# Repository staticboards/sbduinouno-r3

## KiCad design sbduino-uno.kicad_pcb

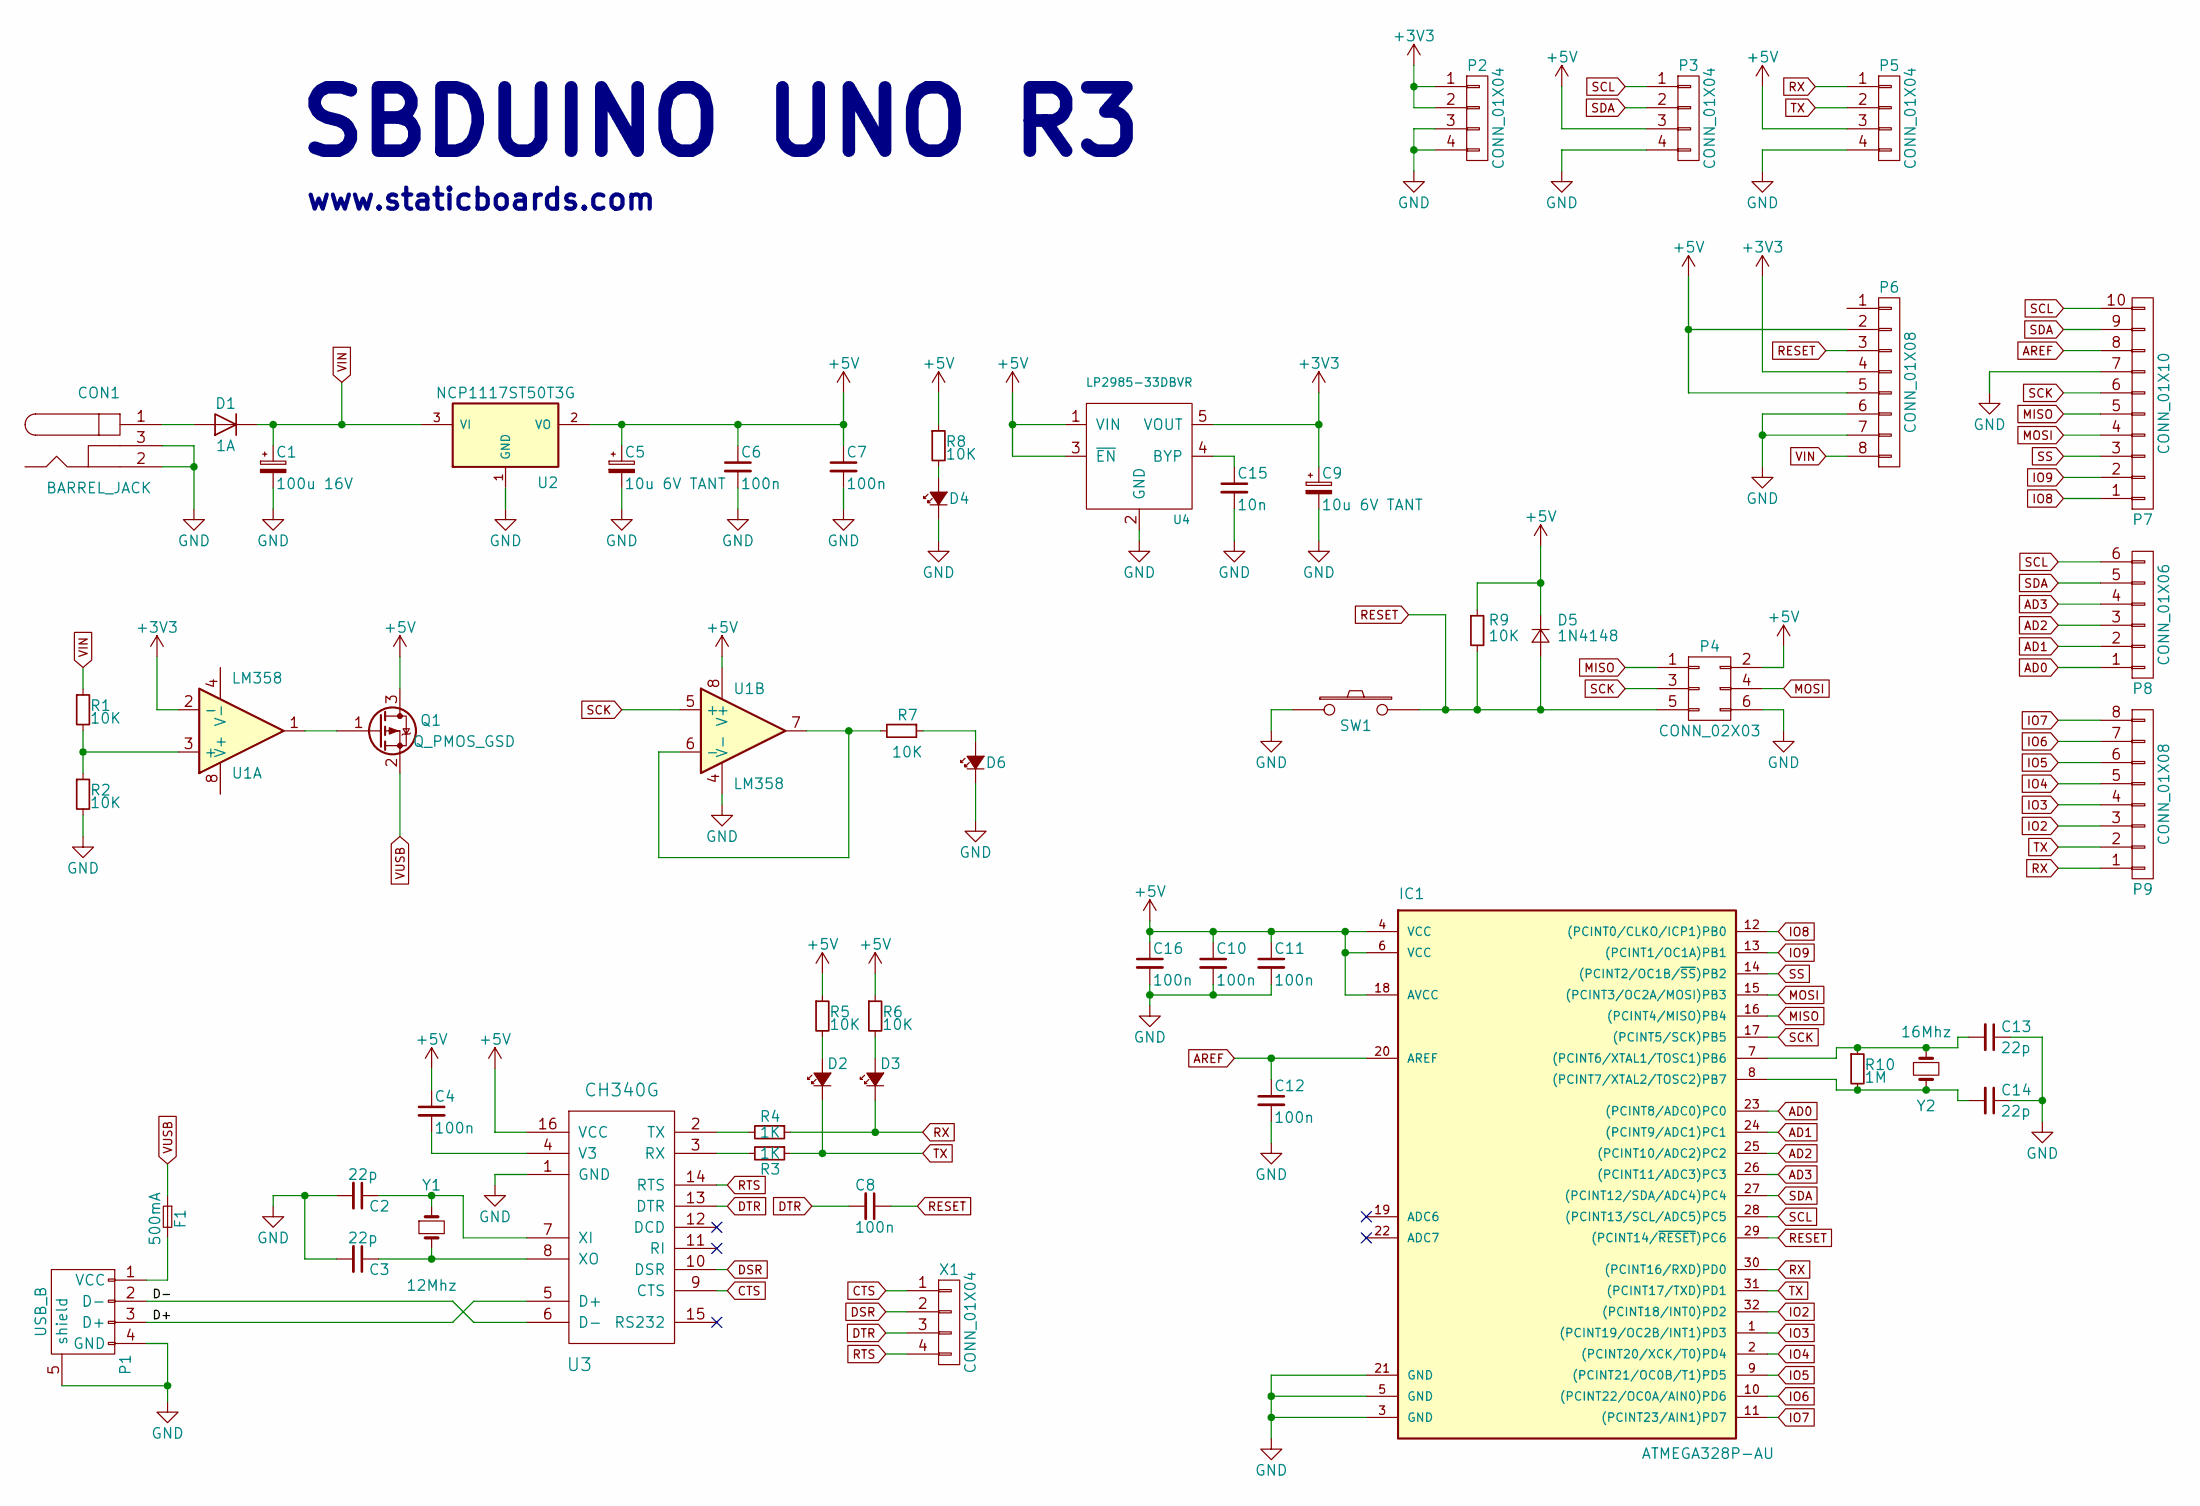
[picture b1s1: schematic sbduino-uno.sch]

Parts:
C1: 100u 16V; CP_Elec_6.3x7.7; Mouser 598-AVE107M25X16T-F
C2, C3, C14: 22p; C_0805
C4, C6, C7, C8, C10, C11, C12, C16: 100n; C_0805
C5, C9: 10u 6V TANT; TantalC_SizeA_EIA-3216_Reflow; Mouser 74-TP3A106K016C1700A
C13: 22p; C_0805; Mouser 81-GRM21A5C2D220JW1D
C15: 10n; C_0805; Mouser 603-CC805MRY5V9BB103
CON1: BARREL_JACK; Mouser 490-PJ-202A
D1: 1A; SMA_Standard; Mouser 625-RS1A-E3
D2, D3, D4: Led_Small; LED_0805
D5: 1N4148; SOD-323; Mouser 621-1N4448WSF-7
D6: Led_Small; LED_0805; Mouser 621-1N4448WSF-7
F1: 500mA; Fuse_SMD1206_Reflow; Mouser 576-1206L050YR
IC1: ATMEGA328P-AU; TQFP-32_7x7mm_Pitch0.8mm
P1: USB_B
P2, P3, P5: CONN_01X04; Pin_Header_Straight_1x04
P4: CONN_02X03; Pin_Header_Straight_2x03
P6, P9: CONN_01X08; Pin_Header_Straight_1x08
P7: CONN_01X10; Pin_Header_Straight_1x10
P8: CONN_01X06; Pin_Header_Straight_1x06
Q1: Q_PMOS_GSD; SOT-23; Mouser 781-SI2301BDS-E3
R1, R2, R5, R6, R7, R8, R9: 10K; R_0805
R3, R4: 1K; R_0805
R10: 1M; R_0805; Mouser 660-RK73H2ATTD1004F
SW1: SW_PUSH; SW_SPST_EVPBF; Mouser 611-PTS645SM43SMTR92
U1: LM358; MSOP-8_3x3mm_Pitch0.65mm; Mouser 595-LMV358IDGKR
U2: NCP1117ST50T3G; SOT-223; Mouser 863-NCP1117ST50T3G
U3: CH340G; SO-16-N
U4: LP2985-33DBVR; SOT-23-5; Mouser 595-LP2985-33DBVR
X1: CONN_01X04; Pin_Header_Straight_1x04
Y1: 12Mhz; Crystal_HC49-SD_SMD; Mouser 815-ABLS-12.0M-T
Y2: 16Mhz; CRYSTAL-SMD-3.2x2.5; Mouser 815-ABM8-16-B2-T

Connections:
+3V3: C9.1, P2.1, P2.2, P6.4, U1.2 (-), U4.5 (VOUT); also elsewhere on the board
+5V: C4.1, C5.1, C6.1, C7.1, C10.1, C11.1, C16.1, D5.1 (K), IC1.4 (VCC), IC1.6 (VCC), IC1.18 (AVCC), P3.3, P4.2, P5.3, P6.2, P6.5, Q1.3 (D), R5.1, R6.1, R8.1, R9.1, U1.8 (V+), U2.2 (VO), U3.16 (VCC), U4.1 (VIN), U4.3 (~EN); also elsewhere on the board
/D+: P1.3 (D+), U3.5 (D+)
/D-: P1.2 (D-), U3.6 (D-)
AD0: IC1.23 ((PCINT8/ADC0)PC0), P8.1; also elsewhere on the board
AD1: IC1.24 ((PCINT9/ADC1)PC1), P8.2; also elsewhere on the board
AD2: IC1.25 ((PCINT10/ADC2)PC2), P8.3; also elsewhere on the board
AD3: IC1.26 ((PCINT11/ADC3)PC3), P8.4; also elsewhere on the board
AREF: C12.1, IC1.20 (AREF), P7.8; also elsewhere on the board
CTS: U3.9 (CTS), X1.1
DSR: U3.10 (DSR), X1.2
DTR: C8.2, U3.13 (DTR), X1.3
GND: C1.2, C2.2, C3.2, C5.2, C6.2, C7.2, C9.2, C10.2, C11.2, C12.2, C13.1, C14.1, C15.2, C16.2, CON1.2, CON1.3, D4.1 (K), D6.1 (K), IC1.3 (GND), IC1.5 (GND), IC1.21 (GND), P1.4 (GND), P1.5 (shield), P2.3, P2.4, P3.4, P4.6, P5.4, P6.6, P6.7, P7.7, R2.2, SW1.1, U1.4 (V-), U2.1 (GND), U3.1 (GND), U4.2 (GND); also elsewhere on the board
IO2: IC1.32 ((PCINT18/INT0)PD2), P9.3; also elsewhere on the board
IO3: IC1.1 ((PCINT19/OC2B/INT1)PD3), P9.4; also elsewhere on the board
IO4: IC1.2 ((PCINT20/XCK/T0)PD4), P9.5; also elsewhere on the board
IO5: IC1.9 ((PCINT21/OC0B/T1)PD5), P9.6; also elsewhere on the board
IO6: IC1.10 ((PCINT22/OC0A/AIN0)PD6), P9.7; also elsewhere on the board
IO7: IC1.11 ((PCINT23/AIN1)PD7), P9.8; also elsewhere on the board
IO8: IC1.12 ((PCINT0/CLKO/ICP1)PB0), P7.1; also elsewhere on the board
IO9: IC1.13 ((PCINT1/OC1A)PB1), P7.2; also elsewhere on the board
MISO: IC1.16 ((PCINT4/MISO)PB4), P4.1, P7.5; also elsewhere on the board
MOSI: IC1.15 ((PCINT3/OC2A/MOSI)PB3), P4.4, P7.4; also elsewhere on the board
unnamed: C2.1, U3.7 (XI), Y1.1
unnamed: C3.1, U3.8 (XO), Y1.2
unnamed: C4.2, U3.4 (V3)
unnamed: C13.2, IC1.7 ((PCINT6/XTAL1/TOSC1)PB6), R10.1, Y2.1
unnamed: C14.2, IC1.8 ((PCINT7/XTAL2/TOSC2)PB7), R10.2, Y2.2
unnamed: C15.1, U4.4 (BYP)
unnamed: CON1.1, D1.2 (A)
unnamed: D2.2 (A), R5.2
unnamed: D3.2 (A), R6.2
unnamed: D4.2 (A), R8.2
unnamed: D6.2 (A), R7.1
unnamed: F1.2, P1.1 (VCC)
unnamed: Q1.1 (G), U1.1
unnamed: R1.2, R2.1, U1.3 (+)
unnamed: R3.2, U3.3 (RX)
unnamed: R4.2, U3.2 (TX)
unnamed: R7.2, U1.6 (-), U1.7
RESET: C8.1, D5.2 (A), IC1.29 ((PCINT14/~RESET~)PC6), P4.5, P6.3, R9.2, SW1.2; also elsewhere on the board
RTS: U3.14 (RTS), X1.4
RX: D3.1 (K), IC1.30 ((PCINT16/RXD)PD0), P5.1, P9.1, R4.1; also elsewhere on the board
SCK: IC1.17 ((PCINT5/SCK)PB5), P4.3, P7.6, U1.5 (+); also elsewhere on the board
SCL: IC1.28 ((PCINT13/SCL/ADC5)PC5), P3.1, P7.10, P8.6; also elsewhere on the board
SDA: IC1.27 ((PCINT12/SDA/ADC4)PC4), P3.2, P7.9, P8.5; also elsewhere on the board
SS: IC1.14 ((PCINT2/OC1B/~SS~)PB2), P7.3; also elsewhere on the board
TX: D2.1 (K), IC1.31 ((PCINT17/TXD)PD1), P5.2, P9.2, R3.1; also elsewhere on the board
VIN: C1.1, D1.1 (K), P6.8, R1.1, U2.3 (VI); also elsewhere on the board
VUSB: F1.1, Q1.2 (S)

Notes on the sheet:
SBDUINO UNO R3
www.staticboards.com

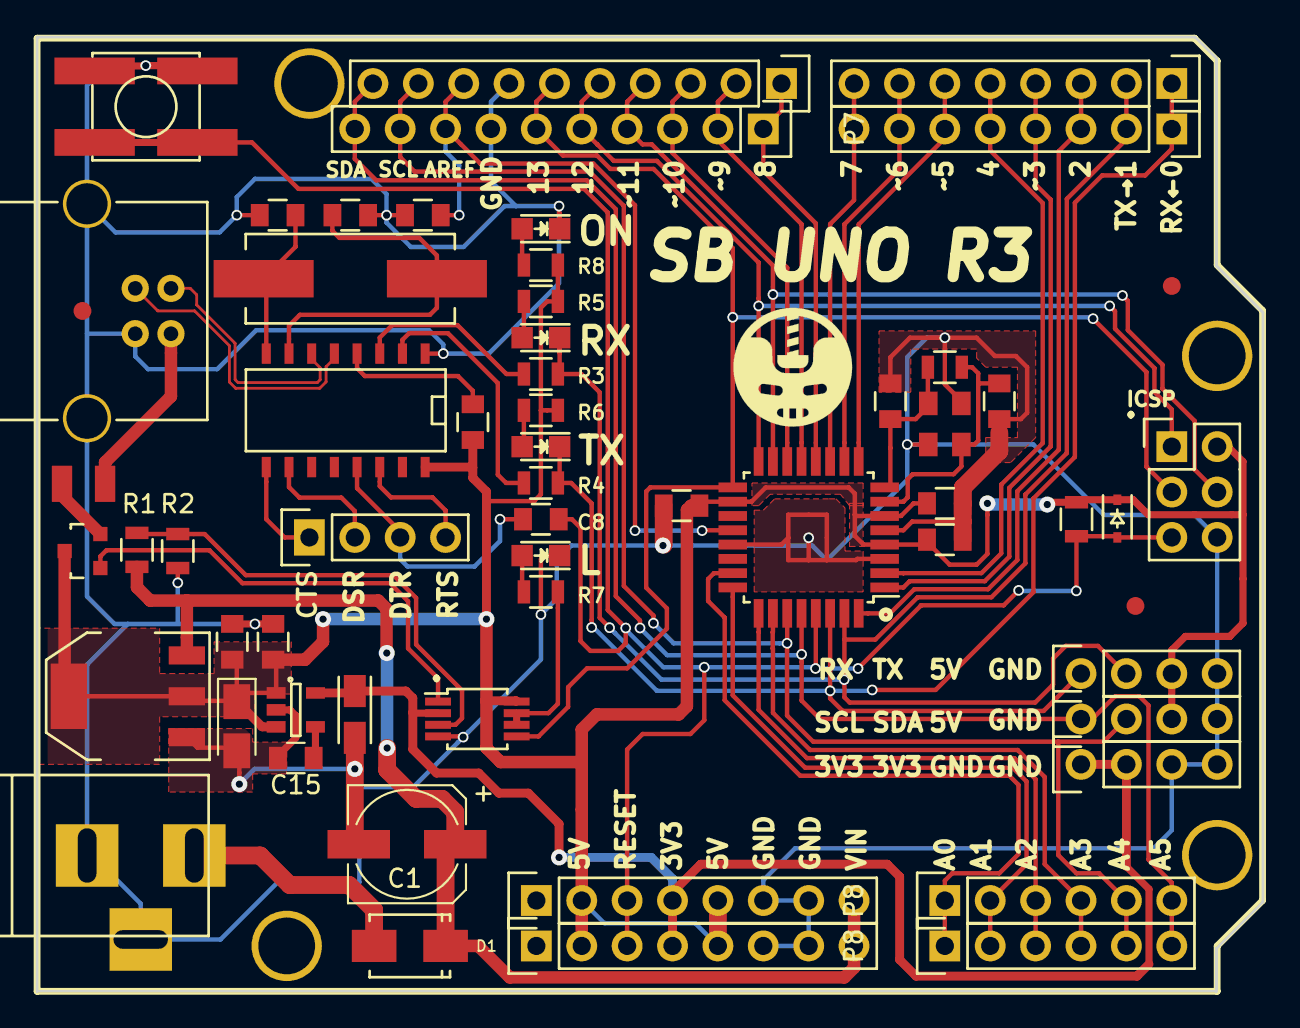
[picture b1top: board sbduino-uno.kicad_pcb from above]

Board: 2 copper layers, 68.6 x 53.4 mm, 58 parts (0 on the bottom side), 50 nets.

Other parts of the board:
P6#2, P9#2: CONN_01X08; Pin_Header_Straight_1x08
P7#2: CONN_01X10; Pin_Header_Straight_1x10
P8#2: CONN_01X06; Pin_Header_Straight_1x06
SHIELD**: ARDUINO_SHIELD

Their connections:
+3V3: P6#2.4; also elsewhere on the board
+5V: P6#2.2, P6#2.5; also elsewhere on the board
AD0: P8#2.1; also elsewhere on the board
AD1: P8#2.2; also elsewhere on the board
AD2: P8#2.3; also elsewhere on the board
AD3: P8#2.4; also elsewhere on the board
AREF: P7#2.8; also elsewhere on the board
GND: P6#2.6, P6#2.7, P7#2.7; also elsewhere on the board
IO2: P9#2.3; also elsewhere on the board
IO3: P9#2.4; also elsewhere on the board
IO4: P9#2.5; also elsewhere on the board
IO5: P9#2.6; also elsewhere on the board
IO6: P9#2.7; also elsewhere on the board
IO7: P9#2.8; also elsewhere on the board
IO8: P7#2.1; also elsewhere on the board
IO9: P7#2.2; also elsewhere on the board
MISO: P7#2.5; also elsewhere on the board
MOSI: P7#2.4; also elsewhere on the board
RESET: P6#2.3; also elsewhere on the board
RX: P9#2.1; also elsewhere on the board
SCK: P7#2.6; also elsewhere on the board
SCL: P7#2.10, P8#2.6; also elsewhere on the board
SDA: P7#2.9, P8#2.5; also elsewhere on the board
SS: P7#2.3; also elsewhere on the board
TX: P9#2.2; also elsewhere on the board
VIN: P6#2.8; also elsewhere on the board

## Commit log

2017-11-20 sbduino
2017-11-20 schematic
2017-11-20 license
2018-11-09 ignore
2018-11-13 library mess
2018-11-13 kicad 5
